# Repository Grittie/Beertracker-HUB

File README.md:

# IoT Start Project

This is your IoT Gitlab project. You can use it to store your code and documentation. 

## Getting Started

This project contains a setup using Docker. This will help you setup all the necessary tools to start developing your IoT project.
Before you run the docker-compose command, make sure you have to make changes to the configuration. You can find these in
the `.env` file.

Now, to install and start your project; run the following command in the root of your project:

```bash
docker-compose up -d
```

If everything runs correctly, you should be able to visit your website at [http://localhost/](http://localhost/).

## Structure

There is a specific structure that you should follow when developing your project. This will help you to keep your project organized and easy to understand.

**Documentation**

All the documentation of your project should be placed in the `docs/` folder. This will be used for your portfolio-website.

```bash
├── docs/
```

**Embedded**

Everything you need to run your embedded application should be placed in the `embedded/` folder. This includes the source code like .ino-files from Arduino.

```bash
├── embedded/
```

**Web**

Everything you need to run your web application should be placed in the `web/` folder. This includes the source code like PHP, HTML, CSS, Javascript and images.

```bash
├── web/
```

You can visit your website by going to [http://localhost/](http://localhost/) in your browser. And you can find your IoT dashboard at [http://localhost/dashboard](http://localhost/dashboard).

## Database details

The database is a MySQL database using MariaDB. You can connect to it using the following details:

| Parameter | Value |
| --- | --- |
| Host | `mariadb` (from PHP) `localhost` (from your laptop) |
| Port | `3306` |
| Username | `root` |
| Password | You can find this in your .env-file. |
| Database | You need to create the database yourself. |

## Pages
The documentation github page can be found [here](https://grittie.github.io/Beertracker-HUB/)

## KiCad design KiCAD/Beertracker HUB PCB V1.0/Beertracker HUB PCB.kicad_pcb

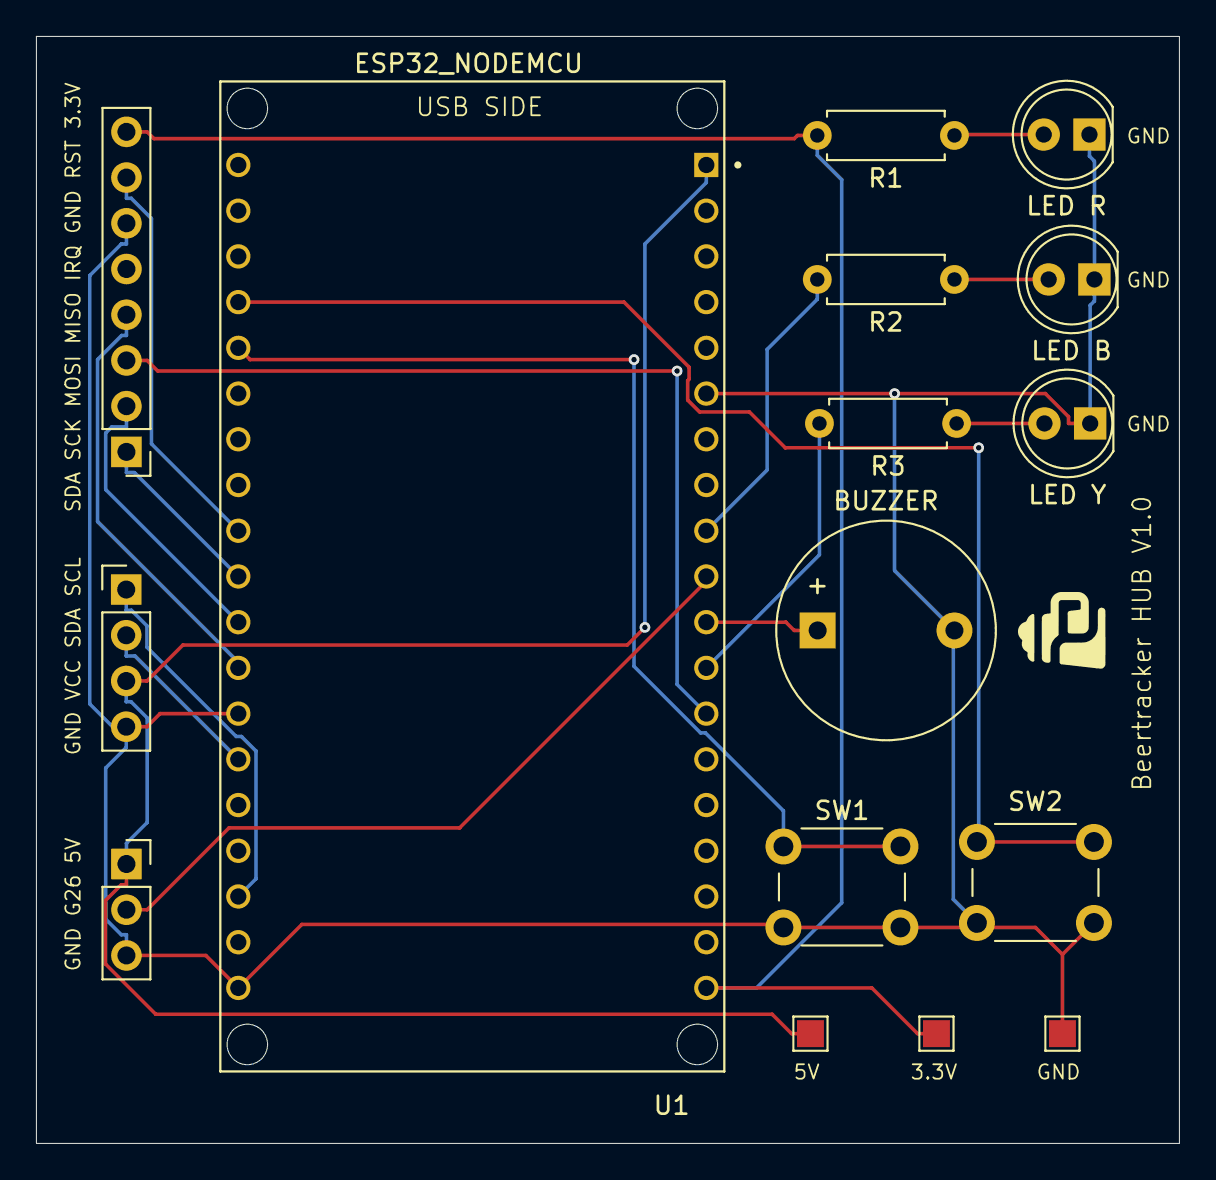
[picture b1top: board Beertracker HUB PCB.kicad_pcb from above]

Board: 2 copper layers, 63.5 x 61.5 mm, 16 parts (0 on the bottom side), 19 nets.

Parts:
BUZZER: Buzzer; Buzzer_12x9.5RM7.6
J1: Conn_01x08_Pin - RC522 RFID; PinHeader_1x08_P2.54mm_Vertical
J2: Conn_01x04_Pin - I2C LCD; PinHeader_1x04_P2.54mm_Vertical
J3: Conn_01x03_Socket - DHT11; PinSocket_1x03_P2.54mm_Vertical
LED B: LED - B; LED_D5.0mm
LED R: LED - R; LED_D5.0mm
LED Y: LED - Y; LED_D5.0mm
R1, R2, R3: R; R_Axial_DIN0207_L6.3mm_D2.5mm_P7.62mm_Horizontal
SW1: SW_Push - minus; SW_PUSH_6mm_H5mm
SW2: SW_Push - Plus; SW_PUSH_6mm_H5mm
TP1: TestPoint GND; TestPoint_Pad_1.5x1.5mm
TP2: TestPoint 3v3; TestPoint_Pad_1.5x1.5mm
TP3: TestPoint 5V; TestPoint_Pad_1.5x1.5mm
U1: ESP32_NODEMCU; MODULE_ESP32_NODEMCU

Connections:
+3.3V: J1.8, R1.2, TP2.1, U1.J5_19 (3V3)
+5V: J2.3, J3.1, TP3.1, U1.J5_1 (5V)
GND: BUZZER.2 (-), J1.6, J2.4, J3.3, LED B.1 (K), LED R.1 (K), LED Y.1 (K), SW1.2, SW2.1, TP1.1, U1.J4_1 (GND_1), U1.J4_7 (GND_7), U1.J5_6 (GND_6)
unnamed: BUZZER.1 (+), U1.J5_11 (G25)
unnamed: LED R.2 (A), R1.1
unnamed: LED B.2 (A), R2.1
unnamed: LED Y.2 (A), R3.1
unnamed: J1.1, U1.J4_10 (G5)
unnamed: J1.2, U1.J4_9 (G18)
unnamed: J1.3, U1.J5_13 (G32)
unnamed: J1.4, U1.J4_8 (G19)
unnamed: J1.7, U1.J4_11 (G17)
unnamed: J2.1, U1.J4_3 (G22)
unnamed: J2.2, U1.J4_6 (G21)
unnamed: J3.2, U1.J5_10 (G26)
unnamed: SW1.1, U1.J4_15 (G2)
unnamed: SW2.2, U1.J4_16 (G15)
unnamed: R2.2, U1.J5_9 (G27)
unnamed: R3.2, U1.J5_12 (G33)

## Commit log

2024-09-02 Project-bestanden van IoT Start Project gekopieerd
2024-09-02 Added submodule mdocotion
2024-09-04 added new favicon!
2024-09-04 added first index.md iteration
2024-09-04 minor spelling & format changes
2024-09-04 markdown list formatting change
2024-09-05 added datasheet for rfid reader
2024-09-05 added basic RFID UID reading implementation
2024-09-05 added images folder in docs/assets
2024-09-05 the rfid scanner now only reads the card once and fires off a LED
2024-09-05 added delay for LED and card registation to avoid accidental registrations
2024-09-05 added fritzing diagrams for RFID scanner
2024-09-05 added a buzzer to the rfid card scanner, and included necessary fritzing schematics
2024-09-05 Testing gitignores
2024-09-05 working localhost version of the portfolio website
2024-09-05 name change in documents
2024-09-06 changed wiring diagrams for RFID scanner from WeMOS to ESP32-S3
2024-09-06 Changed RFID code to work on the esp32 instead of the WeMOS
2024-09-06 added documentation for the requirements in the embedded system
2024-09-06 added the fritzing file to the assets folder
2024-09-06 changed some code blocks
2024-09-06 Added the Technical Documentation for Embedded. Added items to BOM which are currently planned to be used and added WIP diagrams
2024-09-07 added folder for LCD1602
2024-09-07 added more comments and changed beep duration on startup
2024-09-07 added multithreading (tasks) to the RFID code
2024-09-09 added the learners journal and documented week 1, added datasheet for LCD that I mentioned in the learners journal
2024-09-09 added documentation for the database in web and added the sql file
2024-09-09 added ERD, EER and SQL for Database documentation and worked through feedback in learners journal
2024-09-09 succesfully created the database and created a basic website that checks databse connection
2024-09-10 setting up time registration retrieval from database
2024-09-10 Added composer and Dotenv to get database credentials from the .env instead of hardcoding it in there
2024-09-11 written project plan with weekly goals and added SUSE font to the website
2024-09-11 database connection and user information is displayed on the website
2024-09-11 added documentation for web, technical documentation + code
2024-09-11 added feedback and takeaway to learning journal
2024-09-11 fixing image
2024-09-11 added feedback and takeaway for web technical documentation
2024-09-11 added declarations for the RFID code functions and added windows COM ports to the platform.io ini
2024-09-12 added i2c scanner code for the LCD with i2c backpack
2024-09-12 added sample code for the LCD screen
2024-09-13 added wifi manager for ESP32
2024-09-13 updated learning journal with week 2 process
2024-09-13 added more feedback
2024-09-16 combined all modules to create one main iot-embedded project and put the modules in their own directory
2024-09-16 added api files for temp and rfid activity
2024-09-17 moved to single api file structure
2024-09-17 added file
2024-09-17 changed url to ip instead of localhost
2024-09-17 added code for the api that sends the internal temperature from the post request to the database for logging
2024-09-18 adapted all functions into embedded code with internal temp
2024-09-18 fritzing diagram for the updated ESP32 setup
2024-09-19 fixed embedded code for consistent card scanning and temperature logging
2024-09-19 added breathalyser code
2024-09-23 added users to concept & design
2024-09-23 added feedback and take away week 3
2024-09-23 changed and broadend userbase
2024-09-23 updated embedded technical documentation with up to date schematics
2024-09-23 added main goal and product requirements
2024-09-23 improved BOM
2024-09-25 sending UID and returning user name
2024-09-25 changed directory for api file
2024-09-25 added reviews to the learning journal
2024-09-26 added material & digital design to concept_design uxd
2024-09-26 rfid self test
2024-09-26 latest version
2024-09-29 two way comm
2024-09-29 added wifi check function
2024-09-29 changed database setup
2024-09-29 sessions logic receiving
2024-10-01 created session_handler
2024-10-01 changed checkout from hours to minutes incase of attendence but below an hour
2024-10-01 changed dir
2024-10-01 removed redundant total hours calculation
2024-10-01 working sessions logic
2024-10-02 added learning journal
2024-10-02 fixed pathing
2024-10-02 file name changes to follow convention
2024-10-02 added temperature data to the api_ref
2024-10-02 added card and session handlers to the api_ref
2024-10-02 returned get_latest_temp.php
2024-10-02 added esp32-32 folder for testing setting files over
2024-10-03 added the global variables and enabled wifi check
2024-10-03 connection to back-end api
2024-10-03 added connection_handler.php
2024-10-03 added connection status cron job
2024-10-04 moved embedded logic to temp module for new ESP32
2024-10-04 changed pinout and changed necesary values for the new esp32
2024-10-04 changed IP address
2024-10-04 changed LED pinout
2024-10-04 all working pins
2024-10-04 latest commit
2024-10-07 added week 5 learning journal
2024-10-16 documentation
2024-10-16 initializing new rfid module
2024-10-16 added code for new pn532 module
2024-10-16 added lcd implementation with the new rfid module
2024-10-17 added better version control to fritzing diagrams
2024-10-17 added reviews
2024-10-17 updated learning journal with absence
2024-10-18 new pn532 implementation
2024-10-18 added uno pn532 implementation
2024-10-18 added front plate CAD
2024-10-18 front plate V0.2 with bigger hexagons
2024-10-18 front plate v0.3 and v0.4 with better margins and pin replacement
2024-10-18 readjusting pins, filleting pins for stability and creating button cutouts for better fitting
2024-10-19 front-plate version 0.6 with shorter pins, rounded accents and final button placements
2024-10-19 added a rim around the front plate and a spot for the DTH11
2024-10-19 front-plate v0.8 made grid cleaner and symmetrical, changed dht11 placement for better fitting. removed fillet for future lcd extension
2024-10-19 added front and back plate construction, adjusted DHT11 holder and reduced pin size.
2024-10-20 created more threshold in the backplate for a smoother attachments and realigned pins for the DHT11 for better clearance
2024-10-20 changed the housing to have connectors with magnets and created an actual bottom plate for the back-plate to house the micro controlller with gaps for charging ports
2024-10-20 added version 12 of the enclosing with better port positions more threshold for closing and better sizes for the magnets
2024-10-20 added a solid place for the esp32, made holes bigger for the magnets. Made the latching more smooth, and tigthened dth11 placement. and made placement for buzzer
2024-10-20 filleting edges for smoother device feel and look
2024-10-20 added filleting to remove overhang on port cutouts
2024-10-21 added version 1.0 of beertracker hub housing
2024-10-21 added cad to documentation
2024-10-21 working RFID module code
2024-10-22 updated learning journal
2024-10-22 added first version of the LCD plate
2024-10-22 v0.2 of lcd bracket with better fittings
2024-10-23 pinout change
2024-10-23 working embedded side
2024-10-23 moved esp32-32 to main IoT embedded folder
2024-10-24 LCD Plate covering front of LCD
2024-10-24 v0.4 of lcd with better tightness and pins to keep lcd in place
2024-10-24 added system architecture
2024-10-24 initial button menu implementation
2024-10-24 updated button menu with sound queue and smoother button presses with shorter but snappy delay
2024-10-24 LCD display shows the signs of success with different options
2024-10-24 changed session handler logic
2024-10-24 added pitcher clocking
2024-10-25 changed some variables
2024-10-25 added tolerances to backplate and added a backside of the plate for enclosure
2024-10-25 added bootstrap website redesign
2024-10-25 fixed timezones for timestamps
2024-10-26 front-plate v0.16 with supporting structure for the lcd bracket
2024-10-26 LCD plating with rounded corners and less back extrusion
2024-10-27 LCD-plate V0.7 has better tolerances for the mounting and slimmer design body design
2024-10-27 Beertracker HUB Housing V1.2 | NEW LCD Housing, better component placing, cable routing
2024-10-28 added lcd housing to concept_design documentation
2024-10-28 using https tunnel for ip address in esp32 code
2024-10-28 Beertracker HUB housing v1.3 | Added theming
2024-10-29 added learning journal week 8
2024-10-29 added feedback to learning journal
2024-10-30 latest changes
2024-10-30 removed all non local images
2024-10-30 changed datetime from computer date to european nice date
2024-10-30 added heartbeat system
2024-10-31 added latest checked in user
2024-10-31 added mac and ipv4 address of device to website
2024-11-01 added account management
2024-11-01 fixed double error issue on card scanning session handler
2024-11-02 spacing between edit and delete button
2024-11-02 added custom error messages
2024-11-03 changed styling for connect and disconnect
2024-11-04 total data restructuring
2024-11-04 added video of printing process
2024-11-05 set interval on javascript functions for live data
2024-11-05 added navbar redirecting back to dashboard
2024-11-05 implemented HTTP server on esp32 with a reset function on the website
2024-11-07 latest documentation update
2024-11-07 final doc
2024-11-07 added a place for kicad
2024-11-16 new stuff
2024-11-16 fixed serverside issues
2024-11-24 Add GitHub Actions for MkDocs deployment
2024-11-24 updated nodejs
2024-11-24 removed mkdocs-video-plugin
2024-11-24 didn't remove mkdocs-video-plugin from plugins oopsie
2024-11-24 submodule issues
2024-11-24 Fix submodule initialization in GitHub Actions
2024-11-24 Add PYTHONPATH to include mdocotion for macros
2024-11-24 please work
2024-11-24 les do this
2024-11-24 added link for documentation pages
2024-11-24 Deployed b7893c1 with MkDocs version: 1.6.1
2024-12-30 added config.h for credentials for the esp32
2024-12-30 added a documentation for the authentication.h
2024-12-30 changed title
2024-12-30 added PCB design
2024-12-31 added the OLED screen implemenation withhe U8g2 library
2024-12-31 added a duplicate folder for the v1.0
2025-01-01 finalized and ordered PCB design, changed code to be OLED screen orientated
2025-01-01 Deployed 83ea8d5 with MkDocs version: 1.6.1
2025-01-22 refactor OLED screen implementation for improved performance
2025-02-02 Deployed 615dd58 with MkDocs version: 1.6.1
2025-03-14 changed delays
2025-03-14 Deployed 6deba6e with MkDocs version: 1.6.1
